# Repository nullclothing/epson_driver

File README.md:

# Epson Printhead Driver

This is a driver for Epson piezo inkjet printheads, based heavily on Joyce G. Kwan's prior work. It provides a PMOD interface for use with FPGA development boards such as the [iCEBreaker](https://1bitsquared.com/collections/fpga/products/icebreaker). The goal is to enable use of cheap and widespread Epson printheads in DIY projects.

These printheads require an analog signal to actuate the piezos. This signal is actually fairly high voltage/power. It peaks around 33V, and if you're activating all nozzles, you can be supplying over 3A to the printhead. Therefore, we need a DAC with an amplifier capable of supplying that much power. This makes up the bulk of the project.

## Tested on

* Epson XP4105

## References

* [Joyce Kwan's Master's Thesis](https://dspace.mit.edu/bitstream/handle/1721.1/85435/870681346-MIT.pdf?sequence=2_1)

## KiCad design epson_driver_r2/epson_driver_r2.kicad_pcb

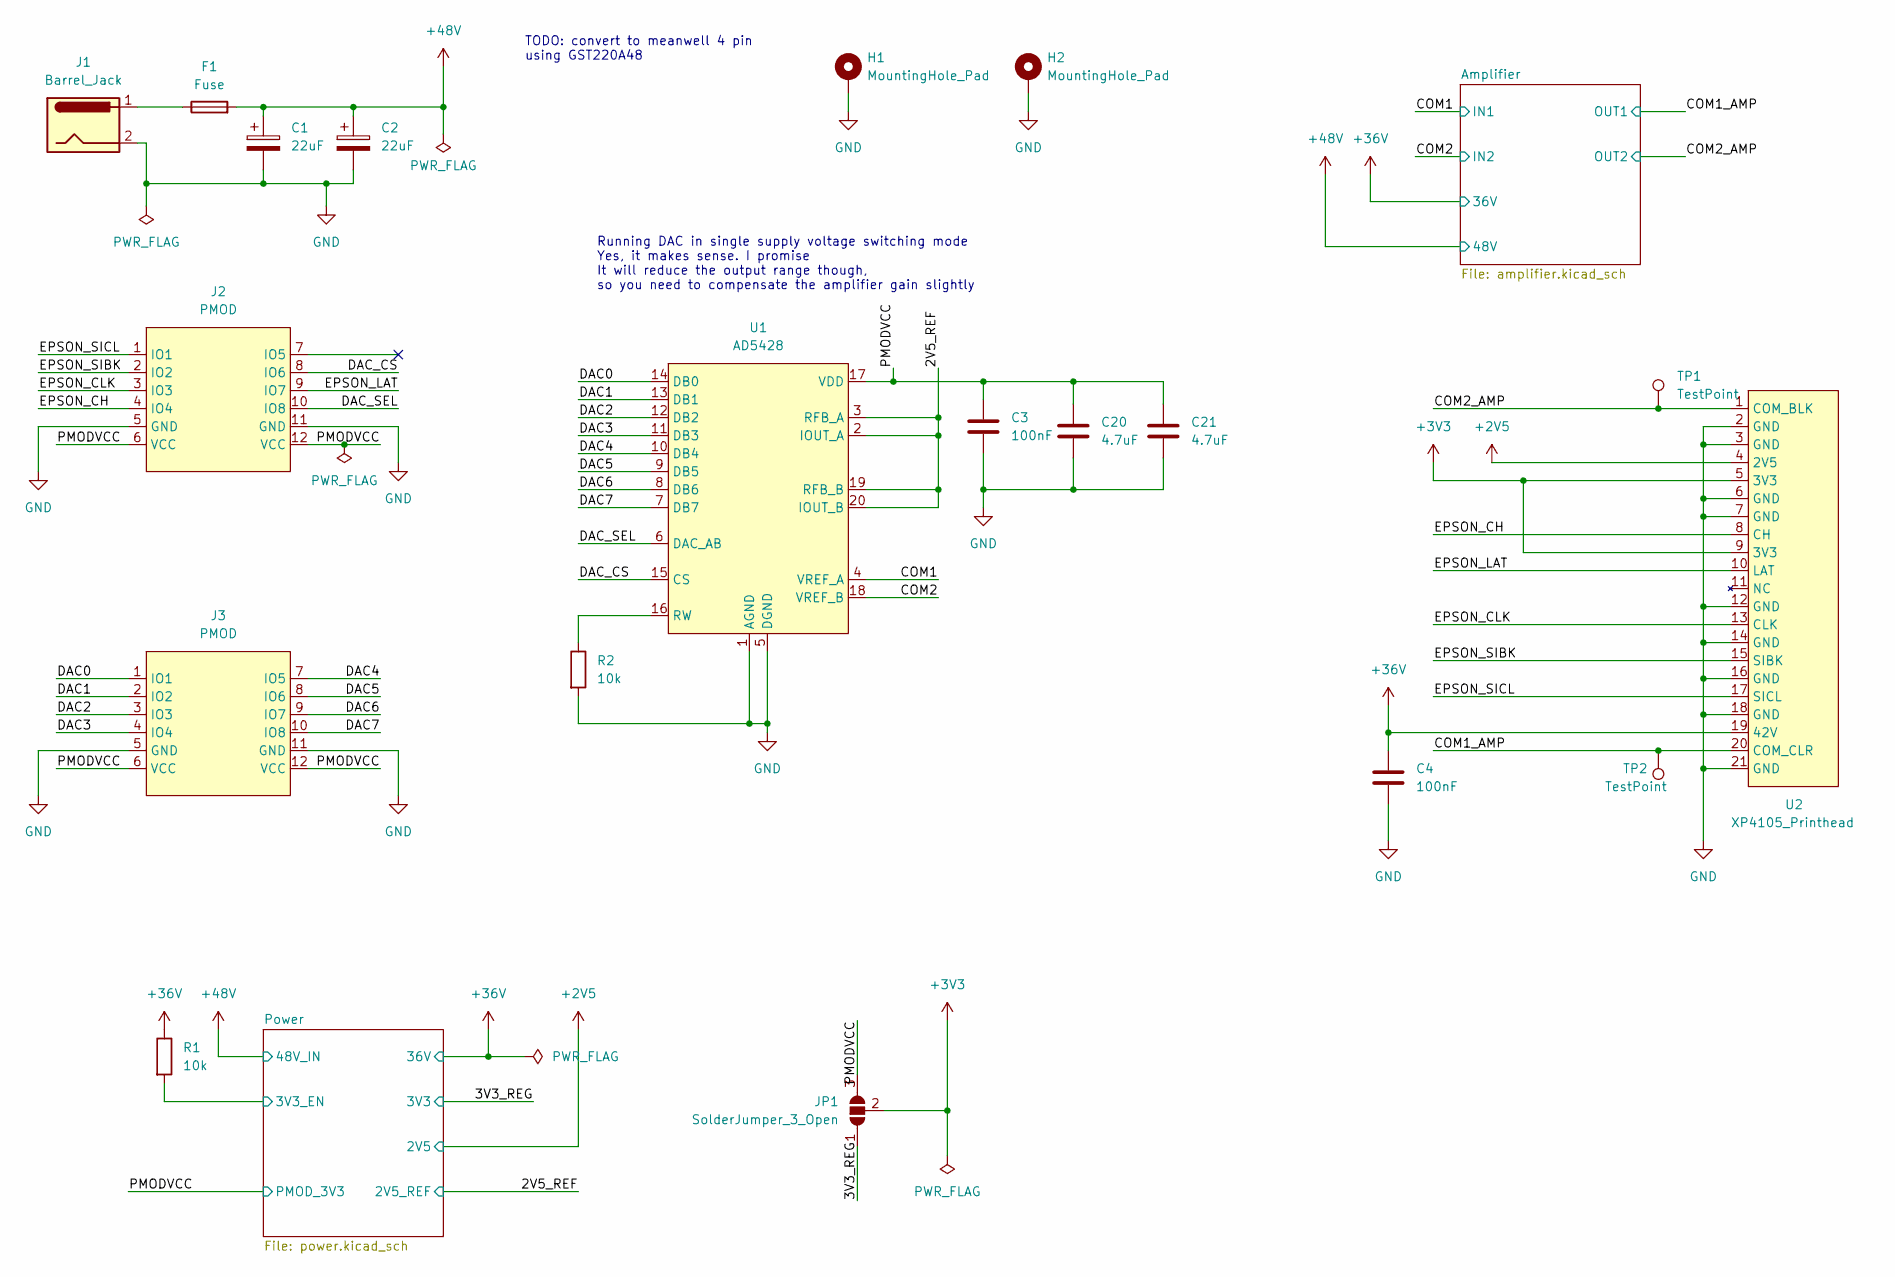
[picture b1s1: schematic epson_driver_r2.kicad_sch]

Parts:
C1, C2: 22uF; CP_Elec_6.3x7.7
C3, C4: 100nF; C_0603_1608Metric_Pad1.08x0.95mm_HandSolder
C20, C21: 4.7uF; C_1206_3216Metric_Pad1.33x1.80mm_HandSolder
F1: Fuse; Fuse_1206_3216Metric_Pad1.42x1.75mm_HandSolder
H1, H2: MountingHole_Pad; MountingHole_3.2mm_M3_Pad_TopBottom
J1: Barrel_Jack; BarrelJack_CUI_PJ-063AH_Horizontal
J2, J3: PMOD; PMOD-12-PERIPHERAL
JP1: SolderJumper_3_Open; SolderJumper-3_P1.3mm_Open_Pad1.0x1.5mm
R1, R2: 10k; R_0603_1608Metric_Pad0.98x0.95mm_HandSolder
TP1, TP2: TestPoint; TestPoint_Pad_D1.0mm
U1: AD5428; TSSOP-20_4.4x6.5mm_P0.65mm
U2: XP4105_Printhead; Molex_200528-0210_1x21-1MP_P1.00mm_Horizontal

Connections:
+2V5: U2.4 (2V5); also elsewhere on the board
+3V3: JP1.2 (C), U2.5 (3V3), U2.9 (3V3)
+36V: C4.1, R1.1, U2.19 (42V); also elsewhere on the board
+48V: C1.1, C2.1, F1.2; also elsewhere on the board
/2V5_REF: U1.2 (IOUT_A), U1.3 (RFB_A), U1.19 (RFB_B), U1.20 (IOUT_B); also elsewhere on the board
/3V3_REG: JP1.1 (A); also elsewhere on the board
/COM1: U1.4 (VREF_A); also elsewhere on the board
/COM1_AMP: TP2.1, U2.20 (COM_CLR); also elsewhere on the board
/COM2: U1.18 (VREF_B); also elsewhere on the board
/COM2_AMP: TP1.1, U2.1 (COM_BLK); also elsewhere on the board
/DAC0: J3.1 (IO1), U1.14 (DB0)
/DAC1: J3.2 (IO2), U1.13 (DB1)
/DAC2: J3.3 (IO3), U1.12 (DB2)
/DAC3: J3.4 (IO4), U1.11 (DB3)
/DAC4: J3.7 (IO5), U1.10 (DB4)
/DAC5: J3.8 (IO6), U1.9 (DB5)
/DAC6: J3.9 (IO7), U1.8 (DB6)
/DAC7: J3.10 (IO8), U1.7 (DB7)
/DAC_CS: J2.8 (IO6), U1.15 (CS)
/DAC_SEL: J2.10 (IO8), U1.6 (DAC_AB)
/EPSON_CH: J2.4 (IO4), U2.8 (CH)
/EPSON_CLK: J2.3 (IO3), U2.13 (CLK)
/EPSON_LAT: J2.9 (IO7), U2.10 (LAT)
/EPSON_SIBK: J2.2 (IO2), U2.15 (SIBK)
/EPSON_SICL: J2.1 (IO1), U2.17 (SICL)
/PMODVCC: C3.1, C20.1, C21.1, J2.6 (VCC), J2.12 (VCC), J3.6 (VCC), J3.12 (VCC), JP1.3 (B), U1.17 (VDD); also elsewhere on the board
/Power/3V3_EN: R1.2; also elsewhere on the board
GND: C1.2, C2.2, C3.2, C4.2, C20.2, C21.2, H1.1, H2.1, J1.2, J2.5 (GND), J2.11 (GND), J3.5 (GND), J3.11 (GND), R2.2, U1.1 (AGND), U1.5 (DGND), U2.2 (GND), U2.3 (GND), U2.6 (GND), U2.7 (GND), U2.12 (GND), U2.14 (GND), U2.16 (GND), U2.18 (GND), U2.21 (GND); also elsewhere on the board
unnamed: F1.1, J1.1
unnamed: R2.1, U1.16 (RW)

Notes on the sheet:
Running DAC in single supply voltage switching mode Yes, it makes sense. I promise It will reduce the output range though, so you need to compensate the amplifier gain slightly
TODO: convert to meanwell 4 pin using GST220A48

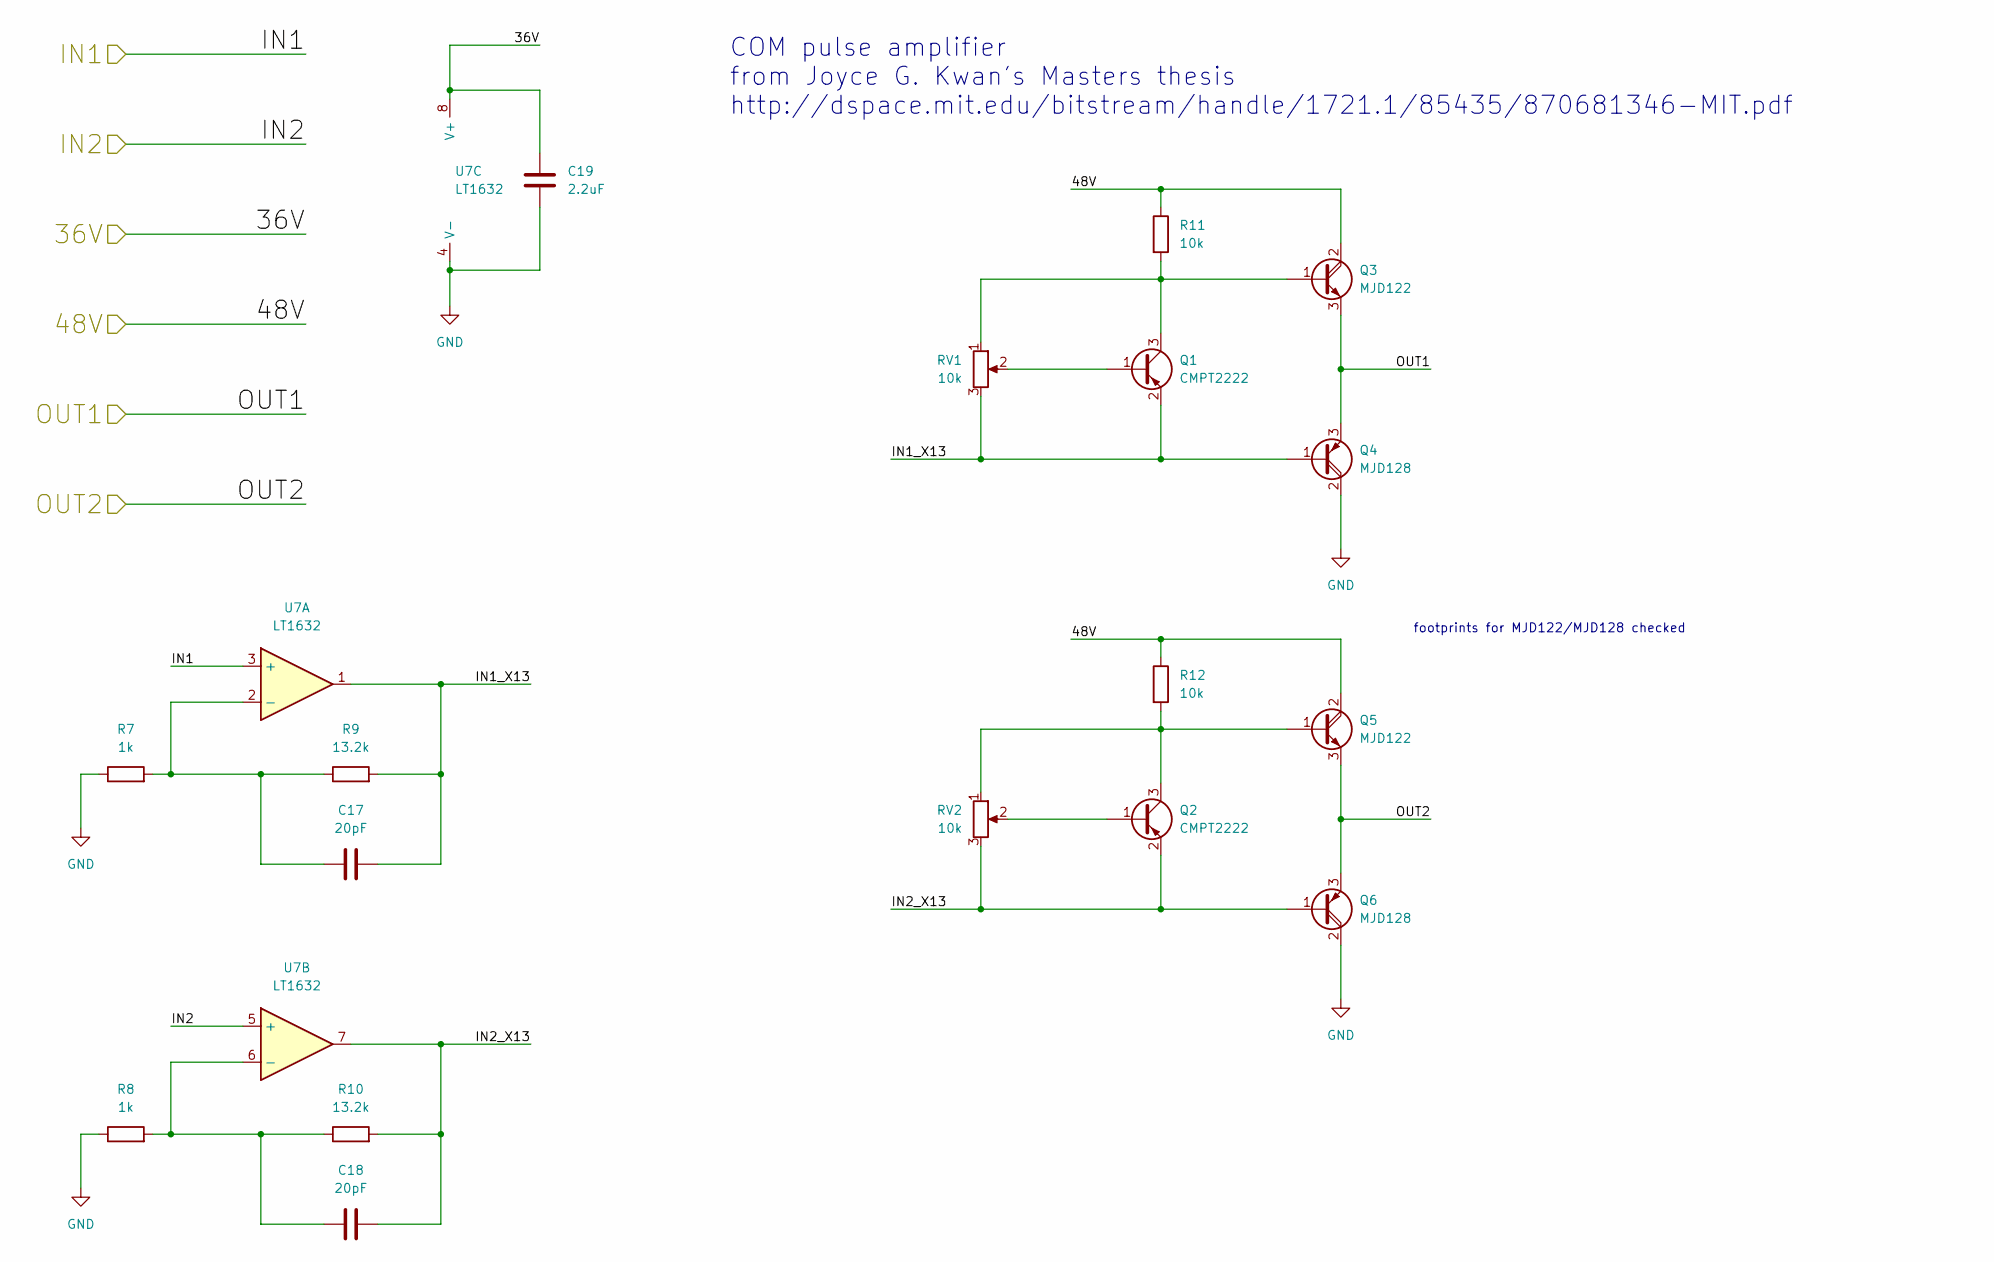
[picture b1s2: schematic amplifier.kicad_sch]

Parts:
C17, C18: 20pF; C_0603_1608Metric_Pad1.08x0.95mm_HandSolder
C19: 2.2uF; C_0603_1608Metric_Pad1.08x0.95mm_HandSolder
Q1, Q2: CMPT2222; SOT-23
Q3, Q5: MJD122; TO-252-3_TabPin2
Q4, Q6: MJD128; TO-252-3_TabPin2
R7, R8: 1k; R_0603_1608Metric_Pad0.98x0.95mm_HandSolder
R9, R10: 13.2k; R_0603_1608Metric_Pad0.98x0.95mm_HandSolder
R11, R12: 10k; R_0603_1608Metric_Pad0.98x0.95mm_HandSolder
RV1, RV2: 10k; Potentiometer_Bourns_3214G_Horizontal
U7: LT1632; SOIC-8_3.9x4.9mm_P1.27mm

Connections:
+36V: C19.1, U7.8 (V+); also elsewhere on the board
+48V: Q3.2 (C), Q5.2 (C), R11.1, R12.1; also elsewhere on the board
/Amplifier/IN1_X13: C17.2, Q1.2 (E), Q4.1 (B), R9.2, RV1.3, U7.1
/Amplifier/IN2_X13: C18.2, Q2.2 (E), Q6.1 (B), R10.2, RV2.3, U7.7
/COM1: U7.3 (+); also elsewhere on the board
/COM1_AMP: Q3.3 (E), Q4.3 (E); also elsewhere on the board
/COM2: U7.5 (+); also elsewhere on the board
/COM2_AMP: Q5.3 (E), Q6.3 (E); also elsewhere on the board
GND: C19.2, Q4.2 (C), Q6.2 (C), R7.1, R8.1, U7.4 (V-); also elsewhere on the board
unnamed: C17.1, R7.2, R9.1, U7.2 (-)
unnamed: C18.1, R8.2, R10.1, U7.6 (-)
unnamed: Q1.1 (B), RV1.2
unnamed: Q1.3 (C), Q3.1 (B), R11.2, RV1.1
unnamed: Q2.1 (B), RV2.2
unnamed: Q2.3 (C), Q5.1 (B), R12.2, RV2.1

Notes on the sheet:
COM pulse amplifier from Joyce G. Kwan's Masters thesis http://dspace.mit.edu/bitstream/handle/1721.1/85435/870681346-MIT.pdf
footprints for MJD122/MJD128 checked

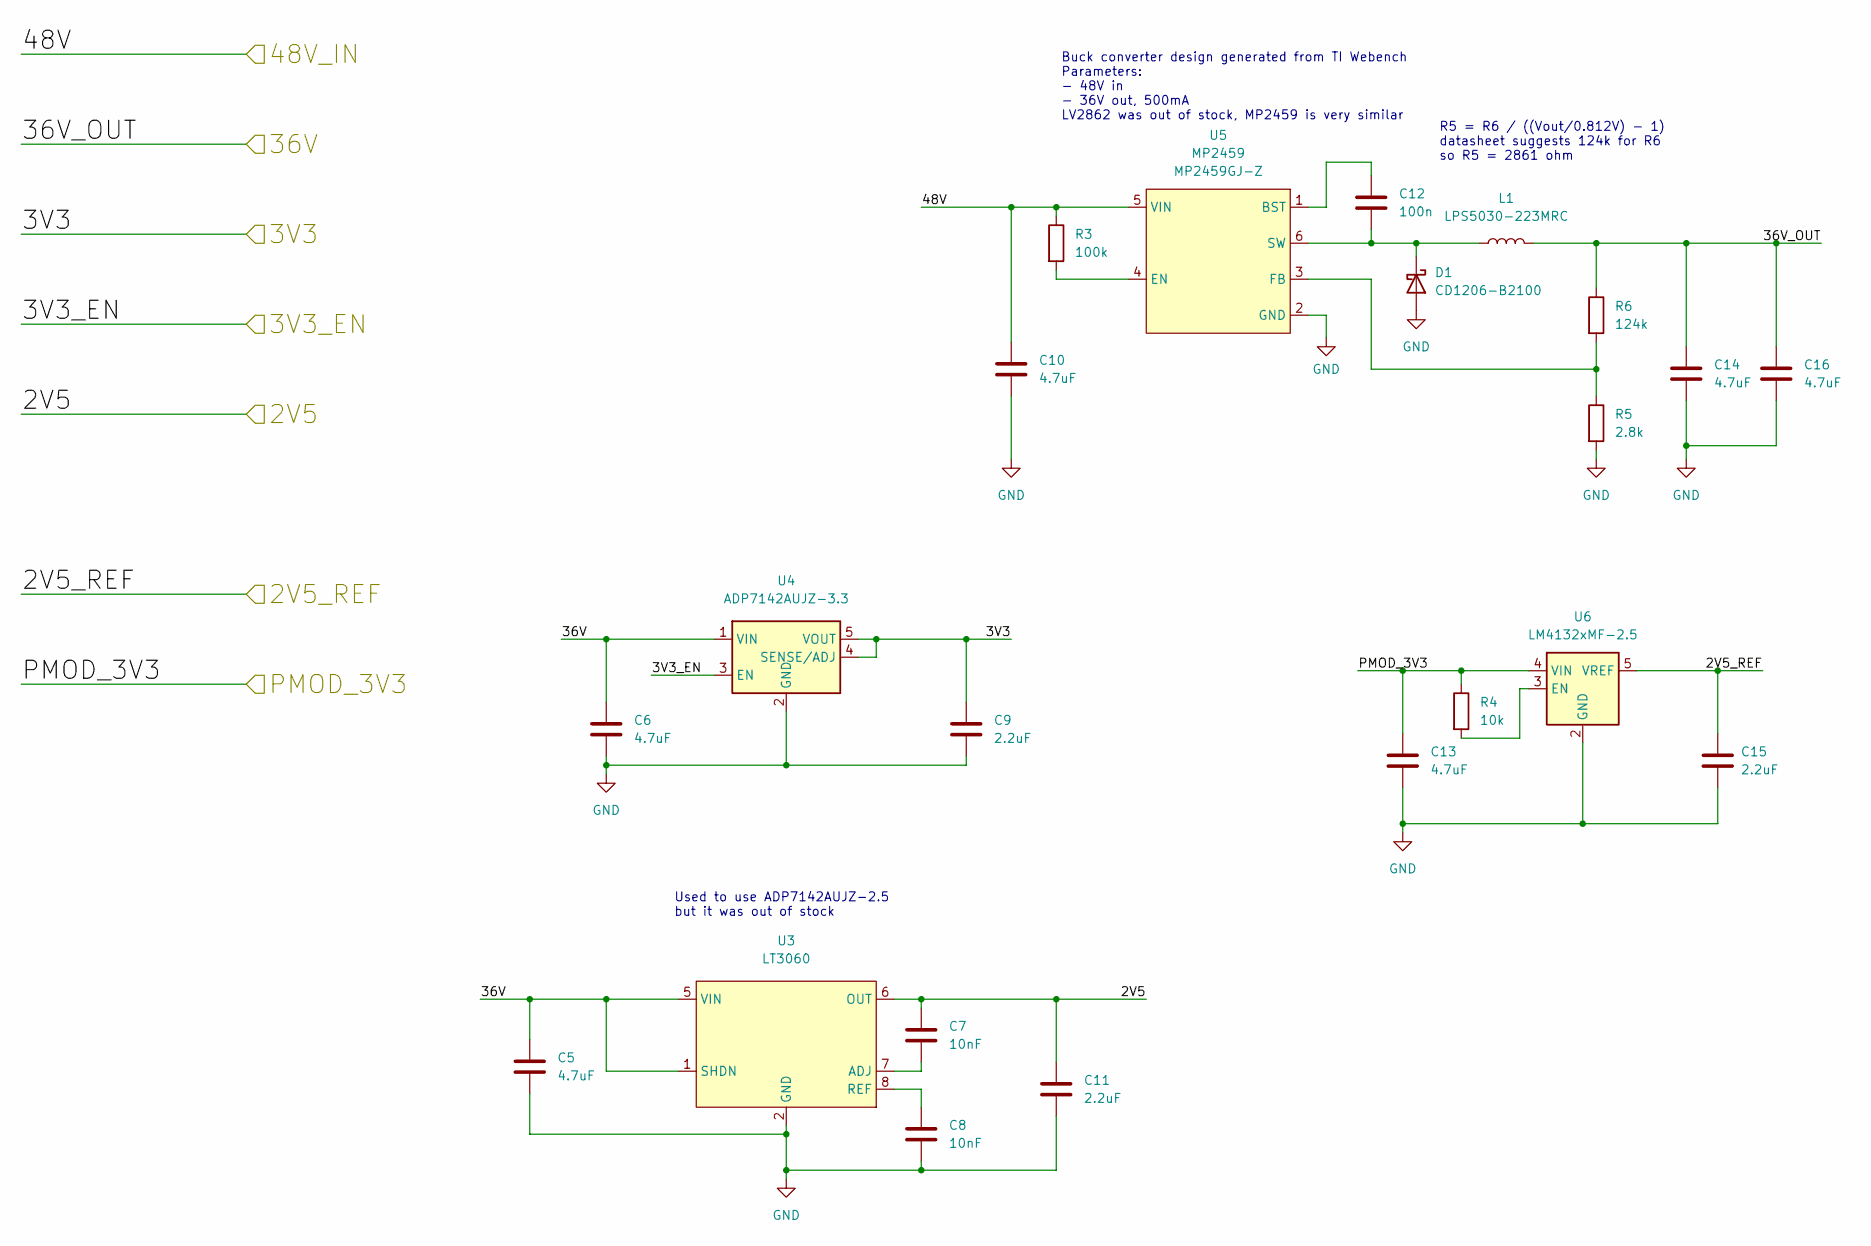
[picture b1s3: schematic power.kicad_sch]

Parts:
C5, C6, C10, C13, C14, C16: 4.7uF; C_1206_3216Metric_Pad1.33x1.80mm_HandSolder
C7, C8: 10nF; C_0603_1608Metric_Pad1.08x0.95mm_HandSolder
C9, C11, C15: 2.2uF; C_0603_1608Metric_Pad1.08x0.95mm_HandSolder
C12: 100n; C_0603_1608Metric_Pad1.08x0.95mm_HandSolder
D1: CD1206-B2100; D_1206_3216Metric_Pad1.42x1.75mm_HandSolder
L1: LPS5030-223MRC; L_Coilcraft_LPS5030
R3: 100k; R_0603_1608Metric_Pad0.98x0.95mm_HandSolder
R4: 10k; R_0603_1608Metric_Pad0.98x0.95mm_HandSolder
R5: 2.8k; R_0603_1608Metric_Pad0.98x0.95mm_HandSolder
R6: 124k; R_0603_1608Metric_Pad0.98x0.95mm_HandSolder
U3: LT3060; SOT-23-8_Handsoldering
U4: ADP7142AUJZ-3.3; TSOT-23-5
U5: MP2459; TSOT-23-6_HandSoldering
U6: LM4132xMF-2.5; SOT-23-5

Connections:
+2V5: C7.1, C11.1, U3.6 (OUT); also elsewhere on the board
+36V: C5.1, C6.1, C14.1, C16.1, L1.2, R6.1, U3.1 (SHDN), U3.5 (VIN), U4.1 (VIN); also elsewhere on the board
+48V: C10.1, R3.1, U5.5 (VIN); also elsewhere on the board
/2V5_REF: C15.1, U6.5 (VREF); also elsewhere on the board
/3V3_REG: C9.1, U4.4 (SENSE/ADJ), U4.5 (VOUT); also elsewhere on the board
/PMODVCC: C13.1, R4.1, U6.4 (VIN); also elsewhere on the board
/Power/3V3_EN: U4.3 (EN); also elsewhere on the board
GND: C5.2, C6.2, C8.2, C9.2, C10.2, C11.2, C13.2, C14.2, C15.2, C16.2, D1.2 (A), R5.2, U3.2 (GND), U3.3 (GND), U3.4 (GND), U4.2 (GND), U5.2 (GND), U6.2 (GND); also elsewhere on the board
unnamed: C7.2, U3.7 (ADJ)
unnamed: C8.1, U3.8 (REF)
unnamed: C12.1, U5.1 (BST)
unnamed: C12.2, D1.1 (K), L1.1, U5.6 (SW)
unnamed: R3.2, U5.4 (EN)
unnamed: R4.2, U6.3 (EN)
unnamed: R5.1, R6.2, U5.3 (FB)

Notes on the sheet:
Buck converter design generated from TI Webench Parameters: - 48V in - 36V out, 500mA LV2862 was out of stock, MP2459 is very similar
R5 = R6 / ((Vout/0.812V) - 1) datasheet suggests 124k for R6 so R5 = 2861 ohm
Used to use ADP7142AUJZ-2.5 but it was out of stock

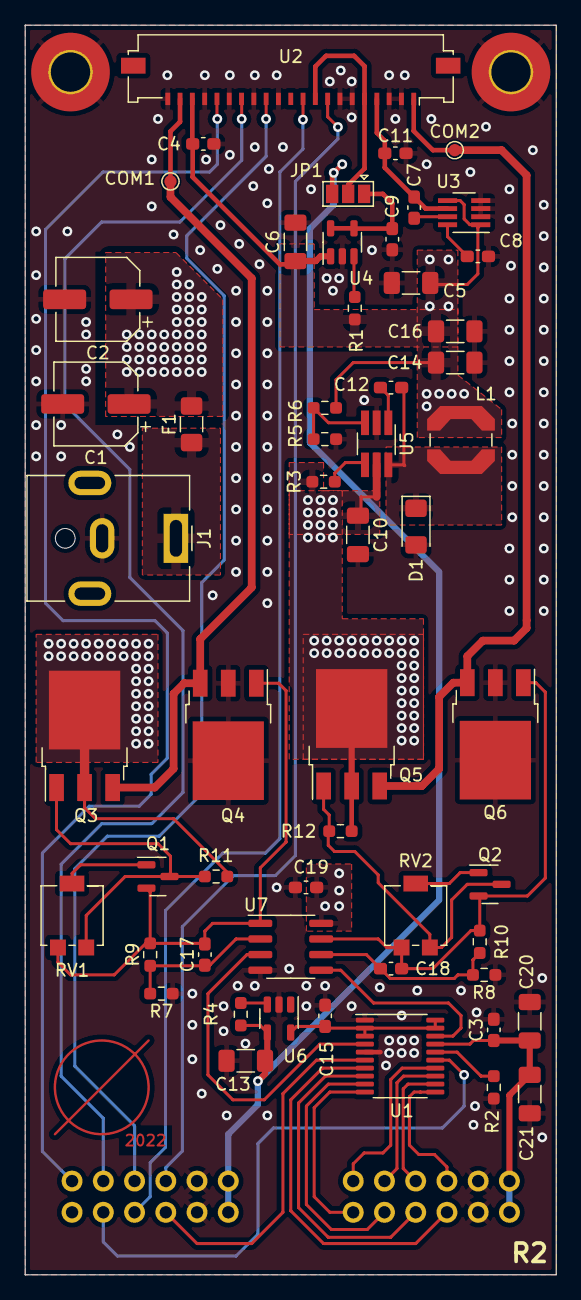
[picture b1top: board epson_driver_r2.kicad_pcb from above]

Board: 4 copper layers, 43.2 x 101.6 mm, 59 parts (0 on the bottom side), 45 nets.

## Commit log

2022-08-21 split out epson driver into its own repo
2022-10-15 make sure flipped PNPs are fixed. need to finalize new board rev
